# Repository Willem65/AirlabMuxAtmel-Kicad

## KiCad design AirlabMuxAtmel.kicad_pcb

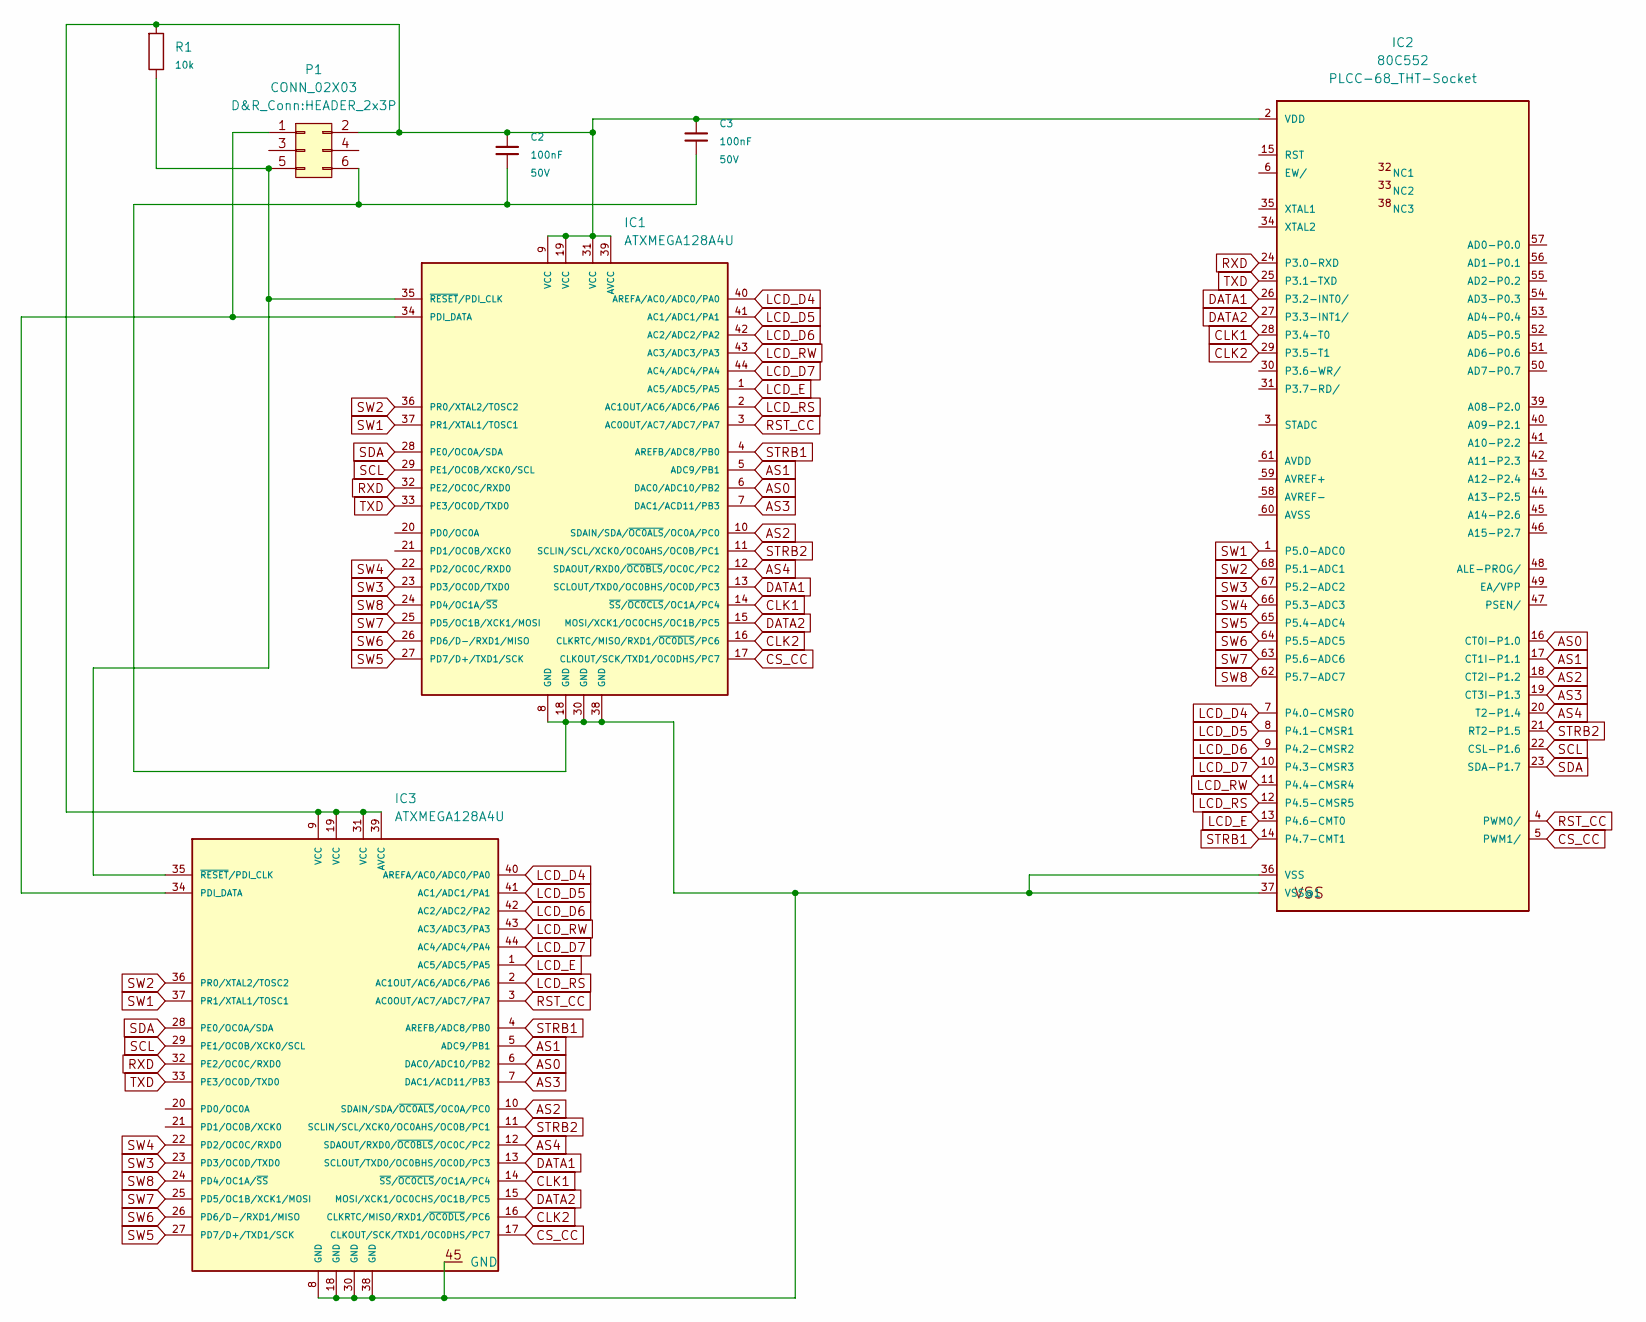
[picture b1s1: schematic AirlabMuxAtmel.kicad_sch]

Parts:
C2, C3: 100N-X7R_50V#0603-D&R_Passive; C_0603; Voltage 50V
IC1: ATXMEGA128A4U#TQFP44; TQFP-44_10x10mm_Pitch0.8mm
IC2: 80C552; PLCC-68_THT-Socket
IC3: ATXMEGA128A4U#TQFP44; QFN50P700X700X100-45N
P1: CONN_02X03; HEADER_2x3P
R1: 0R#0603; R_0603; LCSC C21189

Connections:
AS0: IC1.6 (DAC0/ADC10/PB2), IC2.16 (CT0I-P1.0), IC3.6 (DAC0/ADC10/PB2)
AS1: IC1.5 (ADC9/PB1), IC2.17 (CT1I-P1.1), IC3.5 (ADC9/PB1)
AS2: IC1.10 (SDAIN/SDA/~OC0ALS/OC0A/PC0), IC2.18 (CT2I-P1.2), IC3.10 (SDAIN/SDA/~OC0ALS/OC0A/PC0)
AS3: IC1.7 (DAC1/ACD11/PB3), IC2.19 (CT3I-P1.3), IC3.7 (DAC1/ACD11/PB3)
AS4: IC1.12 (SDAOUT/RXD0/~OC0BLS/OC0C/PC2), IC2.20 (T2-P1.4), IC3.12 (SDAOUT/RXD0/~OC0BLS/OC0C/PC2)
CLK1: IC1.14 (~SS/~OC0CLS/OC1A/PC4), IC2.28 (P3.4-T0), IC3.14 (~SS/~OC0CLS/OC1A/PC4)
CLK2: IC1.16 (CLKRTC/MISO/RXD1/~OC0DLS/PC6), IC2.29 (P3.5-T1), IC3.16 (CLKRTC/MISO/RXD1/~OC0DLS/PC6)
CS_CC: IC1.17 (CLKOUT/SCK/TXD1/OC0DHS/PC7), IC2.5 (PWM1/), IC3.17 (CLKOUT/SCK/TXD1/OC0DHS/PC7)
DATA1: IC1.13 (SCLOUT/TXD0/OC0BHS/OC0D/PC3), IC2.26 (P3.2-INT0/), IC3.13 (SCLOUT/TXD0/OC0BHS/OC0D/PC3)
DATA2: IC1.15 (MOSI/XCK1/OC0CHS/OC1B/PC5), IC2.27 (P3.3-INT1/), IC3.15 (MOSI/XCK1/OC0CHS/OC1B/PC5)
LCD_D4: IC1.40 (AREFA/AC0/ADC0/PA0), IC2.7 (P4.0-CMSR0), IC3.40 (AREFA/AC0/ADC0/PA0)
LCD_D5: IC1.41 (AC1/ADC1/PA1), IC2.8 (P4.1-CMSR1), IC3.41 (AC1/ADC1/PA1)
LCD_D6: IC1.42 (AC2/ADC2/PA2), IC2.9 (P4.2-CMSR2), IC3.42 (AC2/ADC2/PA2)
LCD_D7: IC1.44 (AC4/ADC4/PA4), IC2.10 (P4.3-CMSR3), IC3.44 (AC4/ADC4/PA4)
LCD_E: IC1.1 (AC5/ADC5/PA5), IC2.13 (P4.6-CMT0), IC3.1 (AC5/ADC5/PA5)
LCD_RS: IC1.2 (AC1OUT/AC6/ADC6/PA6), IC2.12 (P4.5-CMSR5), IC3.2 (AC1OUT/AC6/ADC6/PA6)
LCD_RW: IC1.43 (AC3/ADC3/PA3), IC2.11 (P4.4-CMSR4), IC3.43 (AC3/ADC3/PA3)
unnamed: C2.1, C3.1, IC1.9 (VCC), IC1.19 (VCC), IC1.31 (VCC), IC1.39 (AVCC), IC2.2 (VDD), IC3.9 (VCC), IC3.19 (VCC), IC3.31 (VCC), IC3.39 (AVCC), P1.2, R1.1
unnamed: C2.2, C3.2, IC1.8 (GND), IC1.18 (GND), IC1.30 (GND), IC1.38 (GND), IC2.36 (VSS), IC2.37 (VSS@1), IC3.8 (GND), IC3.18 (GND), IC3.30 (GND), IC3.38 (GND), IC3.45 (GND), P1.6
unnamed: IC1.34 (PDI_DATA), IC3.34 (PDI_DATA), P1.1
unnamed: IC1.35 (~RESET/PDI_CLK), IC3.35 (~RESET/PDI_CLK), P1.5, R1.2
RST_CC: IC1.3 (AC0OUT/AC7/ADC7/PA7), IC2.4 (PWM0/), IC3.3 (AC0OUT/AC7/ADC7/PA7)
RXD: IC1.32 (PE2/OC0C/RXD0), IC2.24 (P3.0-RXD), IC3.32 (PE2/OC0C/RXD0)
SCL: IC1.29 (PE1/OC0B/XCK0/SCL), IC2.22 (CSL-P1.6), IC3.29 (PE1/OC0B/XCK0/SCL)
SDA: IC1.28 (PE0/OC0A/SDA), IC2.23 (SDA-P1.7), IC3.28 (PE0/OC0A/SDA)
STRB1: IC1.4 (AREFB/ADC8/PB0), IC2.14 (P4.7-CMT1), IC3.4 (AREFB/ADC8/PB0)
STRB2: IC1.11 (SCLIN/SCL/XCK0/OC0AHS/OC0B/PC1), IC2.21 (RT2-P1.5), IC3.11 (SCLIN/SCL/XCK0/OC0AHS/OC0B/PC1)
SW1: IC1.37 (PR1/XTAL1/TOSC1), IC2.1 (P5.0-ADC0), IC3.37 (PR1/XTAL1/TOSC1)
SW2: IC1.36 (PR0/XTAL2/TOSC2), IC2.68 (P5.1-ADC1), IC3.36 (PR0/XTAL2/TOSC2)
SW3: IC1.23 (PD3/OC0D/TXD0), IC2.67 (P5.2-ADC2), IC3.23 (PD3/OC0D/TXD0)
SW4: IC1.22 (PD2/OC0C/RXD0), IC2.66 (P5.3-ADC3), IC3.22 (PD2/OC0C/RXD0)
SW5: IC1.27 (PD7/D+/TXD1/SCK), IC2.65 (P5.4-ADC4), IC3.27 (PD7/D+/TXD1/SCK)
SW6: IC1.26 (PD6/D-/RXD1/MISO), IC2.64 (P5.5-ADC5), IC3.26 (PD6/D-/RXD1/MISO)
SW7: IC1.25 (PD5/OC1B/XCK1/MOSI), IC2.63 (P5.6-ADC6), IC3.25 (PD5/OC1B/XCK1/MOSI)
SW8: IC1.24 (PD4/OC1A/~SS), IC2.62 (P5.7-ADC7), IC3.24 (PD4/OC1A/~SS)
TXD: IC1.33 (PE3/OC0D/TXD0), IC2.25 (P3.1-TXD), IC3.33 (PE3/OC0D/TXD0)

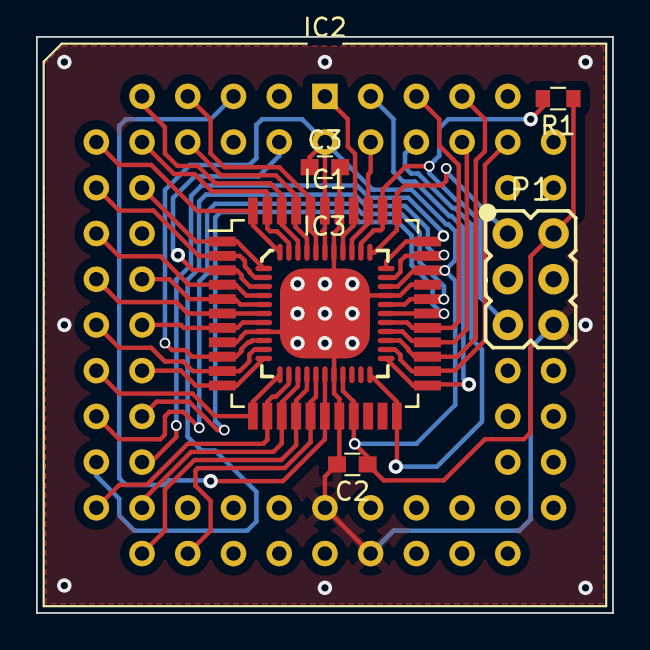
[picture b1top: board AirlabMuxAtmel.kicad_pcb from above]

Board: 2 copper layers, 32.0 x 32.0 mm, 7 parts (0 on the bottom side), 36 nets.

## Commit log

2022-07-13 oke
    oke
2022-07-14 ok
    ok
2022-10-27 28102022
    oke
